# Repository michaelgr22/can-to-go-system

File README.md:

# CAN to go System
## Description
Portable device to stream CAN messages on an App or Browser.

## PCB-Design

## Architecture

## GUI (Browser)

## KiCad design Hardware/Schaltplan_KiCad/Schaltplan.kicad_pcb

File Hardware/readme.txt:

Switch:
https://www.mouser.de/ProductDetail/Gravitech/MINI-SPDT-SW?qs=Vxac6xGyzPm8ENq695r3yA%3D%3D
https://www.mouser.de/ProductDetail/Omron-Electronics/B3FS-1000P?qs=sGAEpiMZZMsqIr59i2oRcmyC8cf5kwrnKCwjdVzpkHM%3D
https://www.digikey.de/de/products/detail/omron-electronics-inc-emc-div/B3F-1020/44059?utm_adgroup=Switches&utm_source=google&utm_medium=cpc&utm_campaign=Shopping_Supplier_Omron%20EMC_0039_Co-op&utm_term=&productid=44059&gclid=EAIaIQobChMIgIj_rIW4_gIVld_tCh2pkg7YEAQYASABEgJWWvD_BwE

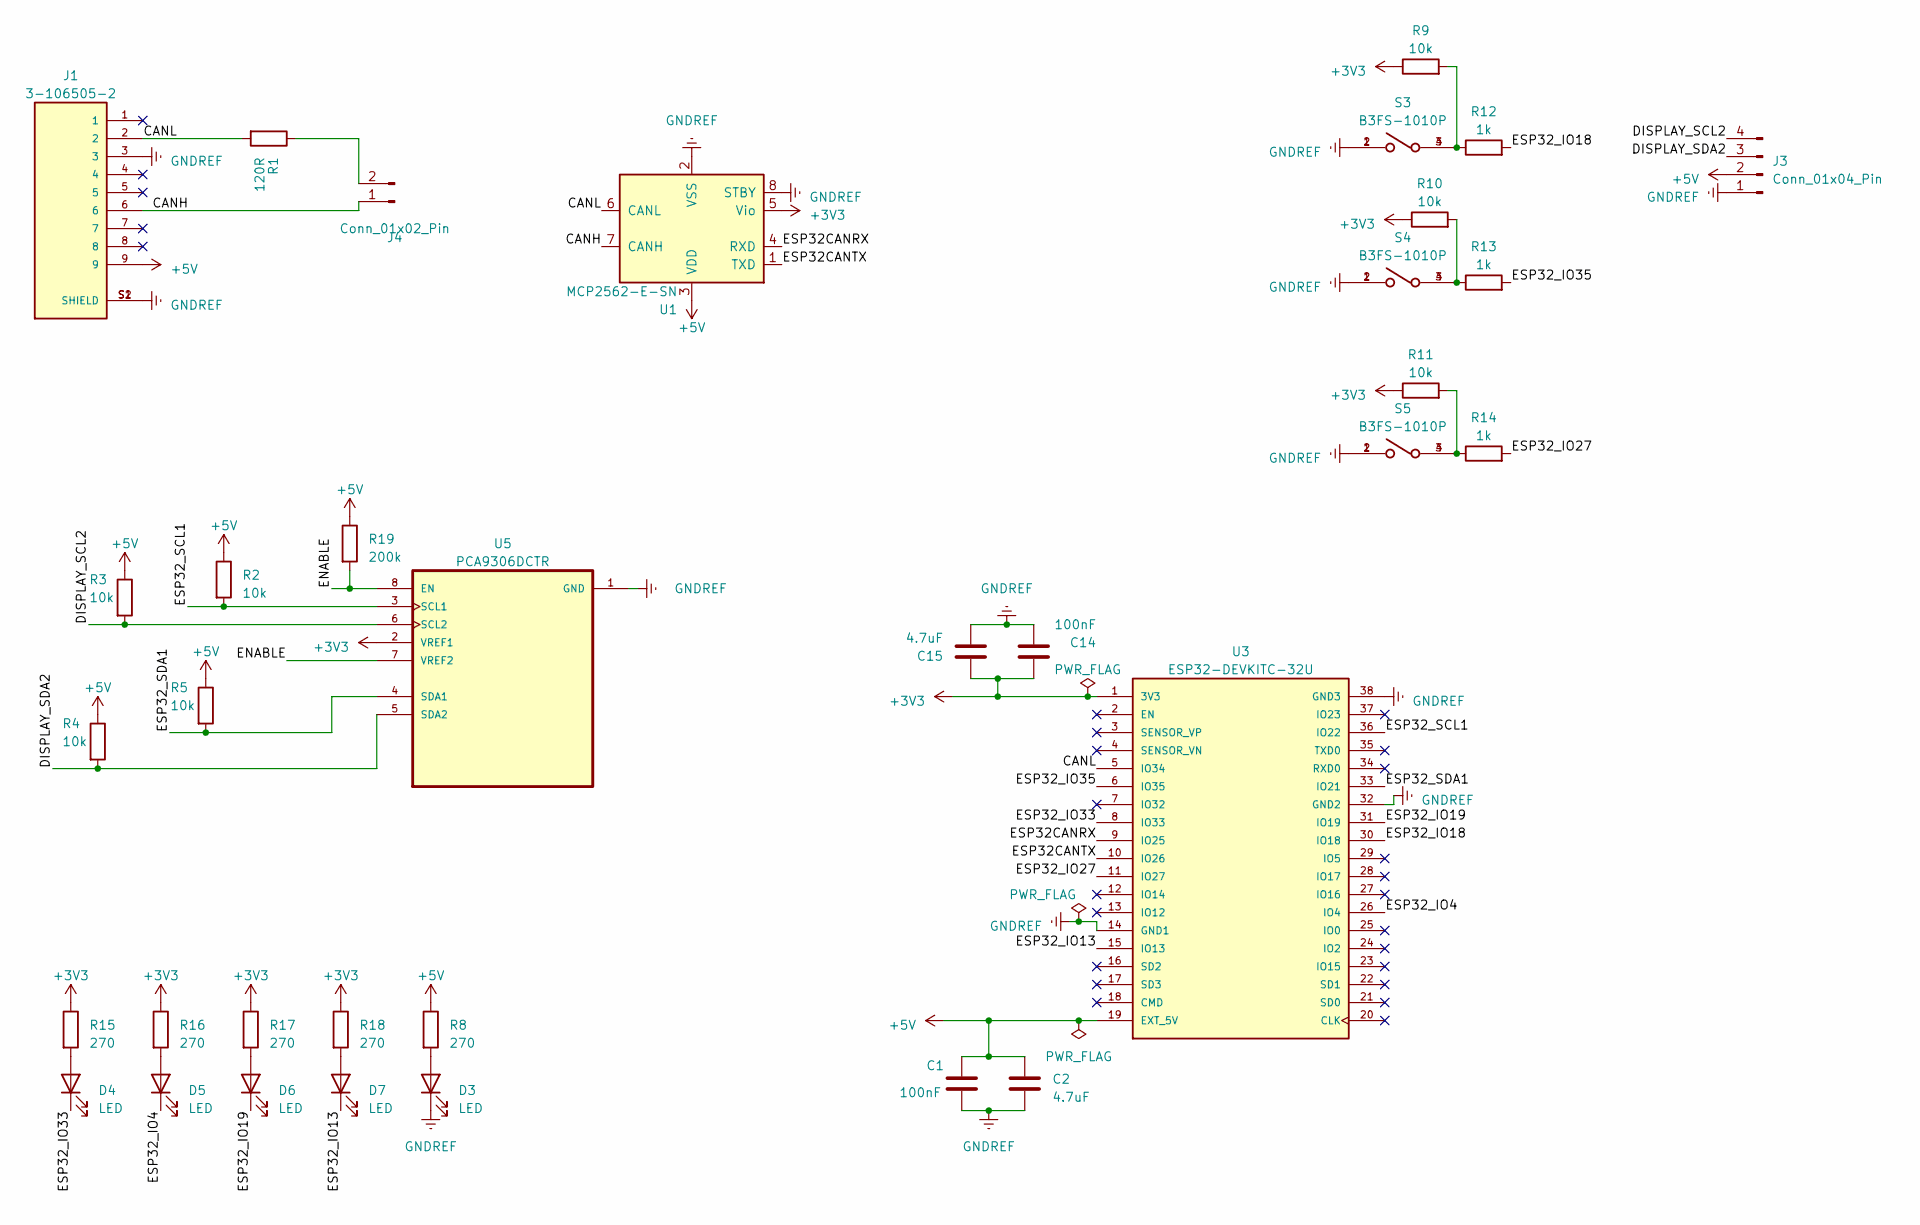
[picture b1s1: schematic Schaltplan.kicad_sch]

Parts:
C1, C14: 100nF; C_0603_1608Metric_Pad1.08x0.95mm_HandSolder
C2, C15: 4.7uF; C_0603_1608Metric_Pad1.08x0.95mm_HandSolder
D3, D4, D5, D6, D7: LED; LED_OF-SMD3528WC
J1: 3-106505-2; TE_3-106505-2
J3: Conn_01x04_Pin; PinHeader_1x04_P2.54mm_Vertical
J4: Conn_01x02_Pin; PinHeader_1x02_P2.54mm_Vertical
R1: 120R; R_0603_1608Metric_Pad0.98x0.95mm_HandSolder
R2, R3, R4, R5, R9, R10, R11: 10k; R_0603_1608Metric_Pad0.98x0.95mm_HandSolder
R8, R15, R16, R17, R18: 270; R_0603_1608Metric_Pad0.98x0.95mm_HandSolder
R12, R13, R14: 1k; R_0603_1608Metric_Pad0.98x0.95mm_HandSolder
R19: 200k; R_0603_1608Metric_Pad0.98x0.95mm_HandSolder
S3, S4, S5: B3FS-1010P; SW_B3FS-1010P
U1: MCP2562-E-SN; DIP-8_W7.62mm
U3: ESP32-DEVKITC-32U; MODULE_ESP32-DEVKITC-32U; PARTREV N/A
U5: PCA9306DCTR; SOP65P400X130-8N

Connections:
+3V3: C14.1, C15.1, R9.1, R10.1, R11.1, R15.1, R16.1, R17.1, R18.1, U1.5 (Vio), U3.1 (3V3), U5.2 (VREF1)
+5V: C1.1, C2.1, J1.9, J3.2, R2.1, R3.1, R4.1, R5.1, R8.1, R19.1, U1.3 (VDD), U3.19 (EXT_5V)
/CANH: J1.6, J4.1, U1.7 (CANH)
/CANL: J1.2, R1.2, U1.6 (CANL), U3.5 (IO34)
/DISPLAY_SCL2: J3.4, R3.2, U5.6 (SCL2)
/DISPLAY_SDA2: J3.3, R4.2, U5.5 (SDA2)
/ENABLE: R19.2, U5.7 (VREF2), U5.8 (EN)
/ESP32CANRX: U1.4 (RXD), U3.9 (IO25)
/ESP32CANTX: U1.1 (TXD), U3.10 (IO26)
/ESP32_IO4: D5.1 (K), U3.26 (IO4)
/ESP32_IO13: D7.1 (K), U3.15 (IO13)
/ESP32_IO18: R12.2, U3.30 (IO18)
/ESP32_IO19: D6.1 (K), U3.31 (IO19)
/ESP32_IO27: R14.2, U3.11 (IO27)
/ESP32_IO33: D4.1 (K), U3.8 (IO33)
/ESP32_IO35: R13.2, U3.6 (IO35)
/ESP32_SCL1: R2.2, U3.36 (IO22), U5.3 (SCL1)
/ESP32_SDA1: R5.2, U3.33 (IO21), U5.4 (SDA1)
GNDREF: C1.2, C2.2, C14.2, C15.2, D3.1 (K), J1.3, J1.S1 (SHIELD), J1.S2 (SHIELD), J3.1, S3.1, S3.2, S4.1, S4.2, S5.1, S5.2, U1.2 (VSS), U1.8 (STBY), U3.14 (GND1), U3.32 (GND2), U3.38 (GND3), U5.1 (GND)
unnamed: D3.2 (A), R8.2
unnamed: D4.2 (A), R15.2
unnamed: D5.2 (A), R16.2
unnamed: D6.2 (A), R17.2
unnamed: D7.2 (A), R18.2
unnamed: J4.2, R1.1
unnamed: R10.2, R13.1, S4.3, S4.4
unnamed: R11.2, R14.1, S5.3, S5.4
unnamed: R9.2, R12.1, S3.3, S3.4

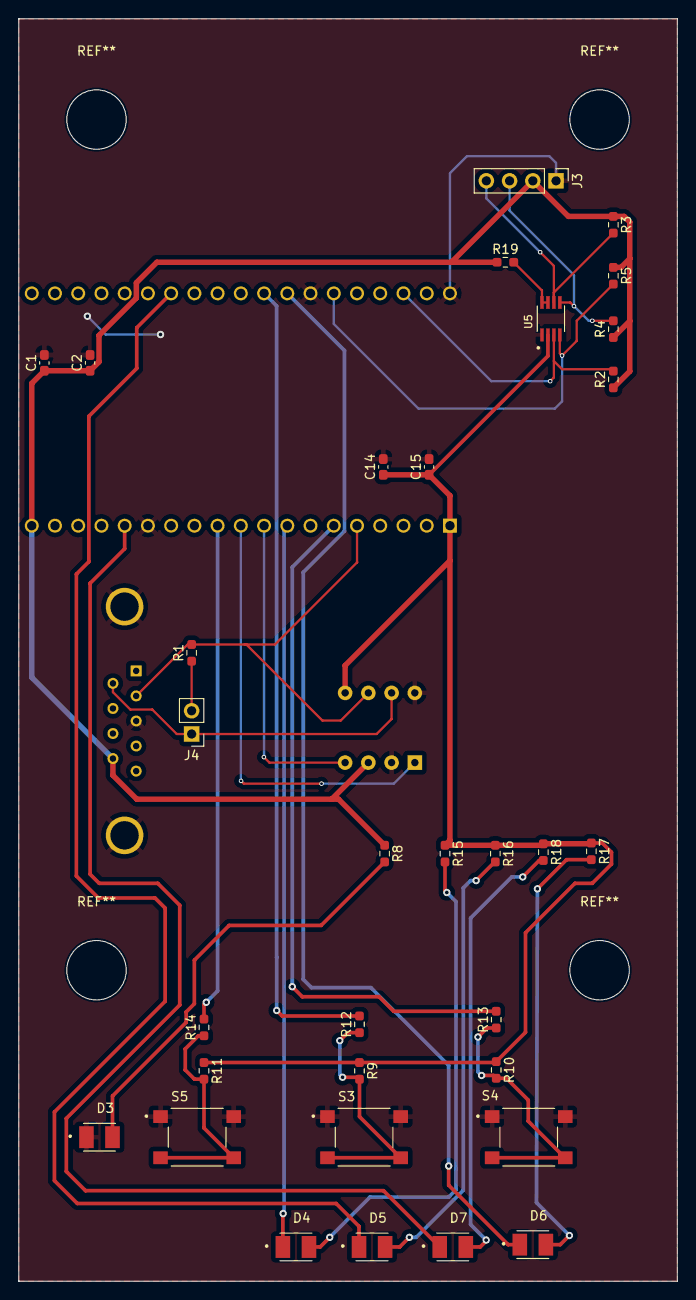
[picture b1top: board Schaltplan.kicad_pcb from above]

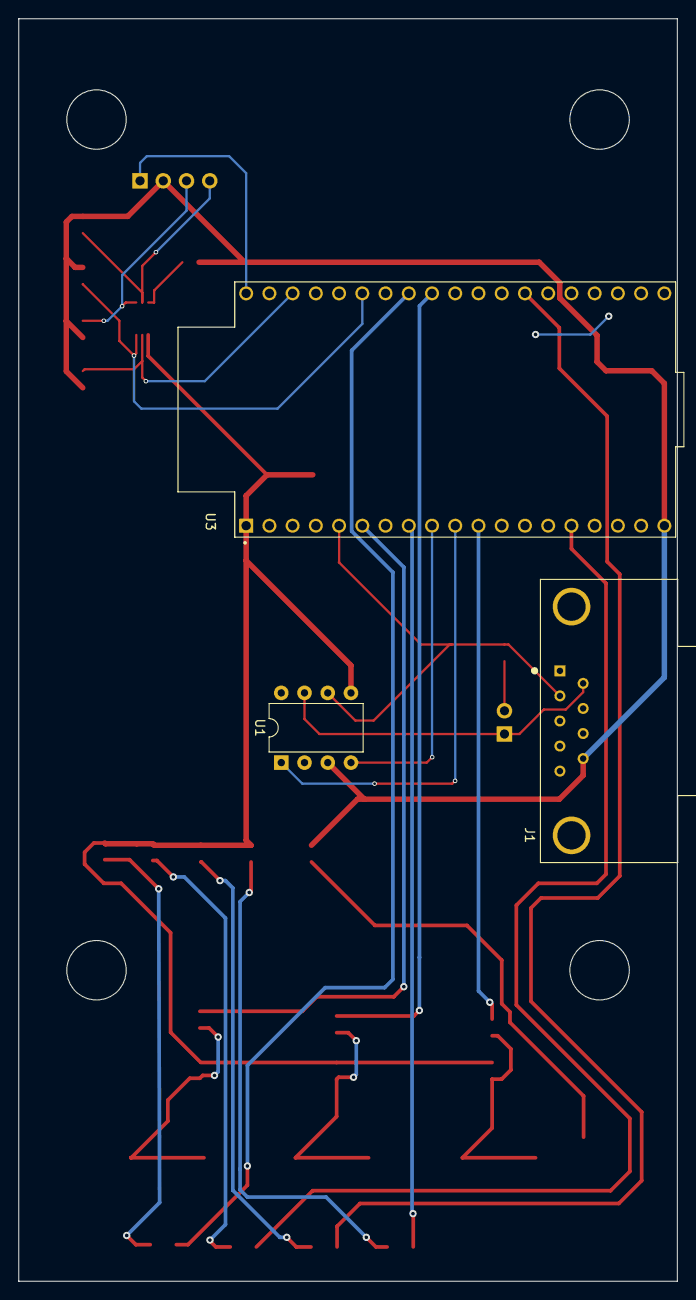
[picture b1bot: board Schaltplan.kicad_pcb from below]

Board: 2 copper layers, 72.0 x 138.0 mm, 35 parts (3 on the bottom side), 28 nets.

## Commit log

2023-04-13 KiCad grundkonfiguration mit paar Teilen
2023-04-13 added CAN sockets with transcievers
2023-04-13 added gitignore for KiCad
2023-04-13 added power supply and uart communication
2023-04-13 added basic description
2023-04-20 added leds, switches and buttons
2023-04-20 added switch and button
2023-04-20 added zwischenpraesenation
2023-05-04 Included Logic Level Shifter with Display
2023-05-04 added missing footprints
2023-05-05 changed switch and ldo
2023-05-06 placed components on pcb
2023-05-06 completed tracing of pcb
2023-05-11 remove battery and redesign
2023-05-12 finishes PCB Design
2023-05-17 verbesserungen und 4te Bohrung und bestellt
2023-05-25 added first hello world sample on espidf
2023-06-09 added example for handling gpios for leds and buttons
2023-06-10 added sample for lcd_display
2023-06-11 added sample for can communication
2023-06-11 created main project
2023-06-11 added first draft of software architecture
2023-06-15 added model for menu item
2023-06-15 added task for uart controller
2023-06-15 created task for display
2023-06-15 fixed baudrate menu
2023-06-15 Bluettooth folder in samples
2023-06-15 parse can baudrate selected to can controller
2023-06-15 moved start of CAN task to Configuration
2023-06-15 fixed header guards after rename
2023-06-15 renamed function to send baudrate via queue
2023-06-16 refactored update_baudrate_menu
2023-06-16 fixed button down and button up pressed handling
2023-06-16 refactored MenuItem to make it more generic
2023-06-16 made presentation of menu more generic
2023-06-16 added fsm controller
2023-06-16 added function to test can bus
2023-06-17 added feature to show can messages on display
2023-06-17 refactoring
2023-06-17 improved formatting
2023-06-17 display only gets updated when can message changed
2023-06-17 added scrolling when more than 4 can ids available
2023-06-17 refactored baudrate menu
2023-06-17 moved models into data folder
2023-06-18 added led controller and function to blink led on received message
2023-06-18 switched to freertos timer becuase esp_timer and freertos timer in parallel breaks can
2023-06-18 implemented led blink on send message
2023-06-18 implemented update of status led for can bus
2023-06-18 reduced time between can test messages
2023-06-21 updated documentation
2023-06-24 Abschlusspraesentation
2023-06-28 updated documenation to current state of implementation
2023-06-29 verbesserte Abschlusspraesentation
2023-11-06 added sample for rest api
2023-11-13 implemented rest api
2023-11-14 created basic gui
2023-11-14 switched back to microseconds
2023-11-15 implemented rest api as datasource
2023-11-15 added android as platform
2023-11-15 overwrite of == operator
2023-11-15 implemented repositories for different usecases
2023-11-16 increased cached and fixed cycle time calculation
2023-11-17 implemented tabs for can overview and trace
2023-11-18 mark newly added messages in trace for better view
2023-11-18 refresh tabs on change
2023-12-20 added doku
2023-12-20 Edited the doku
2023-12-23 updated sequence diagrams
2023-12-24 added images and Einleitung
2023-12-26 Updated LATEX
2023-12-27 modified Hardware
2024-01-03 added pictures
2024-01-03 updated to newest version
2024-01-03 updated references
2024-01-03 added gitignore and untracked unnecessary files
2024-01-03 added software part
2026-01-14 added description and pictures to readme
